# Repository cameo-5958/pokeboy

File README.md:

# Pokeboy

Game Boy handheld with its own emulator and a Gen 1 Pokemon battle AI that runs
on the device. No ROMs in here, bring your own.

## How the AI works

Trainers are driven by a small transformer with a GRU on top. It is integer
only: int8 weights, int16 hidden state, no floats on the device.

The patched ROM runs an unused opcode (`$DB`, `$EB`, `$EC`) wherever the game
would normally pick a trainer's move. The emulator traps it, reads the battle
out of WRAM, runs the model and writes the choice back.

One decision is too slow for a single frame on the Cortex-A8, so the model is
cut into small steps (one GEMM block, one attention head, one GRU step) and the
scheduler fits them in between frames. `ai/models/pep_int.py` is the reference
and the C++ in `pkai/` has to match it bit for bit. There is a test for that.

## Layout

- `gameboy/` emulator core, tests, tools
- `emulator/` frontends: linux, headless, win32
- `pkai/` battle AI
- `pred-patch/` pokered with the opcodes the AI hooks into
- `ai/` simulator, training, weight export
- `buildroot/` device image (PocketBeagle / OSD3358)
- `hardware/` KiCad project
- `app/` Expo app
- `backend/` API for ROMs, mods and cartridge metadata

## Build

```sh
# core, C++17
cmake -S gameboy -B build -DCMAKE_BUILD_TYPE=Release -DPKAI_BUILD_ROM=OFF
cmake --build build -j
build/gbemu_headless game.gb 1800 out.bmp

# patched ROM (needs rgbds) and AI
pred-patch/build_ai.sh
cd ai && uv sync --group dev && sim/build_engine.sh && scripts/build_pkai.sh

# device image
buildroot/scripts/build-image.sh
buildroot/scripts/qemu/run-system.sh

# backend (:4000) and app
cd backend && npm install && npm run dev
cd app && npm install && npm start
```

Most of the `pkai` tests skip themselves until the patched ROM and the weights
have been built.

## License

MIT, see `LICENSE`. `pred-patch/` is the pret/pokered disassembly under its own
terms, see `pred-patch/THIRD_PARTY_NOTICES.md`.

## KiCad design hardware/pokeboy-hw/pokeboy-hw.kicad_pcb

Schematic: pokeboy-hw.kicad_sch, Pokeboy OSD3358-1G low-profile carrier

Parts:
C1: 10n; C_0402_1005Metric
C2, C3, C4, C6, C10: 10u/10V; C_0402_1005Metric
C5, C9, C12, C15, C21, C25, C26, C27: 100n; C_0402_1005Metric
C7, C8: 22u/10V; C_0402_1005Metric
C11: 22u/6.3V; C_0402_1005Metric
C13: 1u/50V; C_0402_1005Metric
C14: 4.7u/10V; C_0402_1005Metric
C16: 220n; C_0402_1005Metric
C20: 10u; C_0402_1005Metric
C22, C23: 220p; C_0402_1005Metric
C24: 1u; C_0402_1005Metric
C102, C103: 18pF; C_0402_1005Metric
C105: 100nF; C_0402_1005Metric
C106: 10uF; C_0805_2012Metric
C107, C108, C109: 22u/10V; C_0805_2012Metric
D1: RED CHARGE; LED_0402_1005Metric
D2: GREEN POWER; LED_0402_1005Metric
D3: 60V Schottky; D_SOD-123F; MPN PMEG6010CEH
FB1, FB2: 600R@100MHz; L_0402_1005Metric
J1: USB Micro-B data/power; USB_Micro-B_Molex-105017-0001; MPN Molex 105017-0001
J2: LiPo 1S + / NTC / -; BATTERY_PADS_3
J3: POWER SWITCH PADS; SWITCH_PADS_2
J4: 8 OHM SPEAKER PADS; SPEAKER_PADS_2
J5: EA WF030-39S; EA_WF030_39S; MPN EA TFT020-23AINN + EA WF030-39S
J6: UART TEST PADS; TEST_PADS_3
J7: RECOVERY SHORT PADS; SHORT_PADS_2
J8: RESET SHORT PADS; SHORT_PADS_2
J9: 104031-0811; microSD_HC_Molex_104031-0811
L1: 0.47uH XFL4015; XFL4015; MPN XFL4015-471ME
L2: 2.2uH >1.5A; L_APV_ANR3012; MPN XFL3012-222MEB
L3: 10uH 1A; LQH43PN; MPN LQH43PN100MR0L
R3: 0R; R_0402_1005Metric
R4: 10k; R_0402_1005Metric; not fitted
R5: 1.78k 1%; R_0402_1005Metric
R6: 3.09k 1%; R_0402_1005Metric
R7: 3.01k 1%; R_0402_1005Metric
R8: 46.4k 1%; R_0402_1005Metric
R9: 10k DNP; R_0402_1005Metric; not fitted
R10, R11: 2.2k; R_0402_1005Metric
R12, R13, R18, R20, R21, R23, R26: 100k; R_0402_1005Metric
R14: 806k 1%; R_0402_1005Metric
R15: 91k 1%; R_0402_1005Metric
R16: 187k 1%; R_0402_1005Metric
R17: 100k 1%; R_0402_1005Metric
R19: 0R DNP; R_0402_1005Metric; not fitted
R22: 10R 1%; R_0402_1005Metric
R27, R28, R29, R30: 33R; R_0402_1005Metric
R31, R32, R104, R105, R106, R107, R108, R109: 10k; R_0402_1005Metric
R33: 1M 1%; R_0402_1005Metric
R34: 330k 1%; R_0402_1005Metric
R102: 1M; R_0402_1005Metric
RN1, RN2, RN3, RN4, RN5, RN6: 4x22R; R_Array_Convex_4x0603
RN7, RN8, RN9, RN10: 100k; R_Array_Convex_4x0603
SW1, SW2, SW3, SW4: EVQ-P1905M
SW5, SW6: B3AL-1001P
SW7, SW8: EVQ-P2B02B
U1: OSD3358-1G-ISM; OSD335X-BGA-256
U2: BQ24074RGT; VQFN-16-1EP_3x3mm_P0.5mm_EP1.6x1.6mm; MPN BQ24074RGT
U3: TPS63802DLAR; TPS63802_DLA10; MPN TPS63802DLAR
U4: TPS62162DSG; WSON-8-1EP_2x2mm_P0.5mm_EP0.9x1.6mm_ThermalVias; MPN TPS62162DSGR
U5: TPS61165DRV; WSON-6-1EP_2x2mm_P0.65mm_EP1x1.6mm; MPN TPS61165DRVR
U6: MAX98357AETE+T; TQFN-16-1EP_3x3mm_P0.5mm_EP1.23x1.23mm
U7: TPD2EUSB30; Texas_DRT-3; MPN TPD2EUSB30DRTR
Y1: 24 MHz; CRYSTAL_5X3.2MM

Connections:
/ADC_VREFN: U1.A9 (AGND_ADC), U1.B9 (VREFN)
/ADC_VREFP: U1.A7 (SYS_ADC_1P8V), U1.B7 (VREFP)
/AMP_EN: R26.1, U1.B4 (XDMA_EVENT_INTR1), U6.4 (SD_MODE)
/AMP_OUT_N: FB2.1, U6.10 (OUTN)
/AMP_OUT_P: FB1.1, U6.9 (OUTP)
/BAT_NTC: J2.2, R9.1, U2.1 (TS)
/BAT_PLUS: C3.1, J2.1, R33.1, U2.2 (BAT), U2.3 (BAT)
/BAT_SENSE: C27.1, R33.2, R34.1, U1.A8 (AIN0)
/BB_EN: R16.2, R17.1, U3.1
/BB_FB: R14.2, R15.1, U3.4
/BB_L1: L1.1, U3.9
/BB_L2: L1.2, U3.7
/BB_MODE: R19.2, R20.1, U3.2
/BB_PG: R18.2, U3.5
/BL_COMP: C16.1, U5.2 (COMP)
/BL_CTRL: R23.1, U1.C3 (MCASP0_AXR1), U5.5 (CTRL)
/BL_SW: D3.1 (K), L3.2, U5.4 (SW)
/BQ_ILIM: R6.1, U2.12 (ILIM)
/BQ_ISET: R5.1, U2.16 (ISET)
/BQ_ITERM: R7.1, U2.15 (ITERM)
/BQ_TMR: R8.1, U2.14 (TMR)
/BTN_A: SW6.1, U1.A13 (SPI0_SCLK)
/BTN_B: SW5.1, U1.A14 (SPI0_CS0)
/BTN_DOWN: SW3.1, U1.A11 (UART1_RXD)
/BTN_LEFT: SW1.1, U1.A3 (MCASP0_ACLKR)
/BTN_RIGHT: SW4.1, U1.A4 (XDMA_EVENT_INTR0)
/BTN_SELECT: SW7.1, U1.B1 (MCASP0_AHCLKR)
/BTN_START: SW8.1, U1.B3 (MCASP0_FSR)
/BTN_UP: SW2.1, U1.A10 (UART1_RTSN)
/BUCK_PG: R21.2, U4.8 (PG)
/BUCK_SW: L2.1, U4.7 (SW)
/CHG_ACTIVE_N: D1.2 (A), R12.2, U1.C13 (UART0_RTSN), U2.9 (~CHG)
/CHG_PGOOD_N: D2.2 (A), R13.2, U1.R7 (GPMC_CSN3), U2.7 (~PGOOD)
/I2S_BCLK: U1.A1 (MCASP0_ACLKX), U6.16 (BCLK)
/I2S_DOUT: U1.B2 (MCASP0_AXR0), U6.1 (DIN)
/I2S_LRCLK: U1.A2 (MCASP0_FSX), U6.14 (LRCLK)
/LCD_CLK_CORE: RN5.3 (R3.1), U1.F1 (LCD_PCLK)
/LCD_CLK_FPC: J5.23, RN5.6 (R3.2)
/LCD_D0_CORE: RN1.1 (R1.1), RN10.8 (R1.2), U1.G3 (LCD_DATA0)
/LCD_D0_FPC: J5.5, RN1.8 (R1.2)
/LCD_D1_CORE: RN1.2 (R2.1), RN10.7 (R2.2), U1.G2 (LCD_DATA1)
/LCD_D1_FPC: J5.6, RN1.7 (R2.2)
/LCD_D2_CORE: RN1.3 (R3.1), RN10.6 (R3.2), U1.G1 (LCD_DATA2)
/LCD_D2_FPC: J5.7, RN1.6 (R3.2)
/LCD_D3_CORE: RN1.4 (R4.1), RN10.5 (R4.2), U1.H3 (LCD_DATA3)
/LCD_D3_FPC: J5.8, RN1.5 (R4.2)
/LCD_D4_CORE: RN2.1 (R1.1), RN9.4 (R4.1), U1.H2 (LCD_DATA4)
/LCD_D4_FPC: J5.9, RN2.8 (R1.2)
/LCD_D5_CORE: RN2.2 (R2.1), RN9.3 (R3.1), U1.H1 (LCD_DATA5)
/LCD_D5_FPC: J5.10, RN2.7 (R2.2)
/LCD_D6_CORE: RN2.3 (R3.1), RN9.2 (R2.1), U1.J3 (LCD_DATA6)
/LCD_D6_FPC: J5.11, RN2.6 (R3.2)
/LCD_D7_CORE: RN2.4 (R4.1), RN9.1 (R1.1), U1.J2 (LCD_DATA7)
/LCD_D7_FPC: J5.12, RN2.5 (R4.2)
/LCD_D8_CORE: RN3.1 (R1.1), RN8.4 (R4.1), U1.J1 (LCD_DATA8)
/LCD_D8_FPC: J5.13, RN3.8 (R1.2)
/LCD_D9_CORE: RN3.2 (R2.1), RN8.3 (R3.1), U1.K3 (LCD_DATA9)
/LCD_D9_FPC: J5.14, RN3.7 (R2.2)
/LCD_D10_CORE: RN3.3 (R3.1), RN8.2 (R2.1), U1.K2 (LCD_DATA10)
/LCD_D10_FPC: J5.15, RN3.6 (R3.2)
/LCD_D11_CORE: RN3.4 (R4.1), RN8.1 (R1.1), U1.K1 (LCD_DATA11)
/LCD_D11_FPC: J5.16, RN3.5 (R4.2)
/LCD_D12_CORE: RN4.1 (R1.1), RN7.4 (R4.1), U1.L3 (LCD_DATA12)
/LCD_D12_FPC: J5.17, RN4.8 (R1.2)
/LCD_D13_CORE: RN4.2 (R2.1), RN7.3 (R3.1), U1.L2 (LCD_DATA13)
/LCD_D13_FPC: J5.18, RN4.7 (R2.2)
/LCD_D14_CORE: RN4.3 (R3.1), RN7.2 (R2.1), U1.L1 (LCD_DATA14)
/LCD_D14_FPC: J5.19, RN4.6 (R3.2)
/LCD_D15_CORE: RN4.4 (R4.1), RN7.1 (R1.1), U1.M3 (LCD_DATA15)
/LCD_D15_FPC: J5.20, RN4.5 (R4.2)
/LCD_D16_CORE: RN5.1 (R1.1), U1.P7 (GPMC_AD15)
/LCD_D16_FPC: J5.21, RN5.8 (R1.2)
/LCD_D17_CORE: RN5.2 (R2.1), U1.T6 (GPMC_AD14)
/LCD_D17_FPC: J5.22, RN5.7 (R2.2)
/LCD_DE_CORE: RN5.4 (R4.1), U1.E1 (LCD_AC_BIAS_EN)
/LCD_DE_FPC: J5.24, RN5.5 (R4.2)
/LCD_HSYNC_CORE: RN6.1 (R1.1), U1.F2 (LCD_HSYNC)
/LCD_HSYNC_FPC: J5.25, RN6.8 (R1.2)
/LCD_VSYNC_CORE: RN6.2 (R2.1), U1.F3 (LCD_VSYNC)
/LCD_VSYNC_FPC: J5.26, RN6.7 (R2.2)
/LED_A: C13.1, D3.2 (A), J5.2
/LED_CHG_A: D1.1 (K), R10.2
/LED_K: J5.1, R22.1, U5.1 (FB)
/LED_PG_A: D2.1 (K), R11.2
/NPOR: J8.1, R32.2, U1.R11 (WARMRSTN)
/OSD_1V8: U1.F10 (SYS_VDD_1P8V), U1.G10 (SYS_VDD_1P8V), U1.H10 (SYS_VDD_1P8V), U1.H11 (SYS_VDD_1P8V), U1.J10 (SYS_VDD_1P8V), U1.J11 (SYS_VDD_1P8V), U1.K10 (SYS_VDD_1P8V), U1.L10 (SYS_VDD_1P8V)
/OSD_3V3A: J9.4, R12.1, R13.1, R18.1, R32.1, R104.2, R105.2, R106.2, R107.2, R108.2, R109.2, U1.F8 (SYS_VDD3_3P3V), U1.F9 (VDDSHV4), U1.G8 (SYS_VDD3_3P3V), U1.G9 (VDDSHV5), U1.H7 (SYS_VDD3_3P3V), U1.H8 (SYS_VDD3_3P3V), U1.H9 (VDDSHV6), U1.J7 (SYS_VDD3_3P3V), U1.J8 (SYS_VDD3_3P3V), U1.J9 (VDDSHV1), U1.K8 (SYS_VDD3_3P3V), U1.K9 (VDDSHV2), U1.L8 (SYS_VDD3_3P3V), U1.L9 (VDDSHV3)
/OSD_3V3AUX: U1.F11 (SYS_VDD2_3P3V), U1.G11 (SYS_VDD2_3P3V)
/OSD_3V3B: C105.1, RN7.7 (R2.2), RN9.5 (R4.2), RN10.4 (R4.1), U1.F6 (SYS_VDD1_3P3V), U1.F7 (SYS_VDD1_3P3V), U1.G6 (SYS_VDD1_3P3V), U1.G7 (SYS_VDD1_3P3V)
/OSD_OSC_IN: C102.1, R102.1, U1.P16 (OSC0_IN), Y1.2
/OSD_OSC_OUT: C103.1, R102.2, U1.N16 (OSC0_OUT), Y1.1
/OSD_RTC_1V8: U1.K11 (SYS_RTC_1P8V), U1.L11 (SYS_RTC_1P8V)
/OSD_SYS: C107.1, C108.1, C109.1, U1.K6 (SYS_VOUT), U1.K7 (SYS_VOUT), U1.L6 (SYS_VOUT), U1.L7 (SYS_VOUT)
/PMIC_PGOOD: U1.N12 (PMIC_PGOOD), U1.P11 (PWRONRSTN)
/PMIC_PWR_EN: U1.N10 (PMIC_POWER_EN), U1.N11 (PMIC_PWR_EN)
/PWR_SW: J3.2, R16.1
/RECOVERY: J7.1, U1.C1 (TDI)
/RTC_PWRONRSTN: U1.N4 (PMIC_LDO_PGOOD), U1.N5 (RTC_PWRONRSTN)
/SD_CD_N: J9.9, R109.1, U1.C14 (SPI0_CS1)
/SD_CLK: J9.5, U1.B15 (MMC0_CLK)
/SD_CMD: J9.3, R108.1, U1.B16 (MMC0_CMD)
/SD_D0: J9.7, R104.1, U1.A16 (MMC0_DAT0)
/SD_D1: J9.8, R105.1, U1.A15 (MMC0_DAT1)
/SD_D2: J9.1, R106.1, U1.C16 (MMC0_DAT2)
/SD_D3: J9.2, R107.1, U1.C15 (MMC0_DAT3)
/SPK_N: C23.1, FB2.2, J4.2
/SPK_P: C22.1, FB1.2, J4.1
/SYS_5V: C7.1, C8.1, C9.1, C10.1, C14.1, C15.1, C20.1, C21.1, C106.1, L3.1, R14.1, U1.P10 (VIN_AC), U1.R10 (VIN_AC), U1.T10 (VIN_AC), U3.6, U4.2 (VIN), U4.3 (EN), U5.6 (VIN), U6.7 (VDD), U6.8 (VDD)
/SYS_BAT: C4.1, C6.1, J3.1, R10.1, R11.1, U2.10 (OUT), U2.11 (OUT), U3.10
/TFT_DC: J5.32, R29.2
/TFT_DC_CORE: R29.1, U1.C5 (ECAP0_IN_PWM0_OUT)
/TFT_RESET: J5.33, R30.2, R31.2
/TFT_RESET_CORE: R30.1, U1.C12 (UART0_CTSN)
/TFT_SCL: J5.31, R27.2
/TFT_SCL_CORE: R27.1, U1.C10 (I2C0_SCL)
/TFT_SDA: J5.29, R28.2
/TFT_SDA_CORE: R28.1, U1.C11 (I2C0_SDA)
/UART0_RX: J6.2, U1.A12 (UART0_RXD)
/UART0_TX: J6.1, U1.B12 (UART0_TXD)
/USB_VBUSDET: C1.1, R3.2, R4.1, U1.J16 (USB0_VBUS)
/VIN_BAT: U1.N7 (PMIC_BAT_SENSE), U1.P8 (VIN_BAT), U1.R8 (VIN_BAT), U1.T8 (VIN_BAT)

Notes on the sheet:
DESIGN INTENT: panel covers the 30x30 mm Core1106; the carrier aperture clears underside parts. The modelled top envelope is about 2.6 mm, leaving ~0.6 mm nominal in a 3.2 mm cavity. Specify inside-corner radius <=0.75 mm and validate solder standoff, display fit, and thermals on first article.
DISPLAY FIRMWARE: RGB666 data D0-D17 plus CLK/DE/HSYNC/VSYNC. ST7789V serial setup uses SDA/SCL/D-C/RESET; RGB-mode CS and TE are intentionally not connected. Initial timing target: ~17 MHz pixel clock, HS 30/HBP 30/HFP 60, VS 4/VBP 4/VFP 8; validate against the exact panel lot.

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
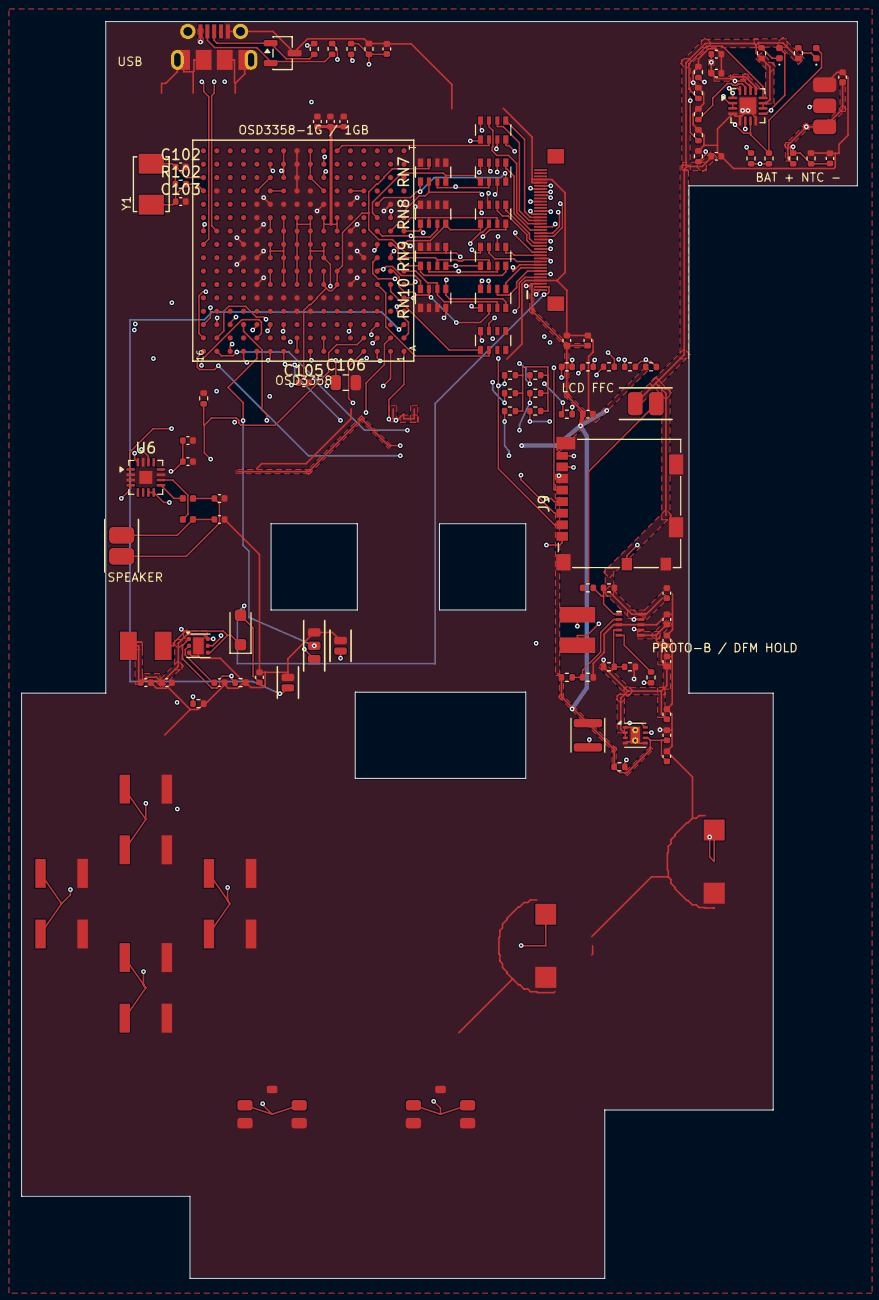
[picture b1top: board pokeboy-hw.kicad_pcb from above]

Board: 4 copper layers, 79.4 x 119.4 mm, 113 parts (0 on the bottom side), 128 nets.

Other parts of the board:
R1, R2: 0R; R_0402_1005Metric

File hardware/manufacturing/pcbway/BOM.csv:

Item,Qty,Designators,Value,Footprint,Manufacturer,Manufacturer Part Number,Assembly,Substitution note
1,1,U1,AM3358 + 1GB DDR3L,21x21mm 256-BGA 1.27mm,Octavo Systems,OSD3358-1G-ISM,SMT BGA,No substitution; consign; X-ray
2,1,U2,1S Li-ion charger/power path,VQFN-16,Texas Instruments,BQ24074RGT,SMT,No substitution
3,1,U3,5V buck-boost,TPS63802 DLA10,Texas Instruments,TPS63802DLAR,SMT,No substitution
4,1,U4,3.3V buck,WSON-8,Texas Instruments,TPS62162DSGR,SMT,No substitution
5,1,U5,LED boost,WSON-6,Texas Instruments,TPS61165DRVR,SMT,No substitution
6,1,U6,I2S mono class-D,TQFN-16,Analog Devices,MAX98357AETE+T,SMT,No substitution
7,1,U7,USB ESD,SOT-23,Texas Instruments,TPD2EUSB30DRTR,SMT,No substitution
8,1,J1,Micro-USB B,105017 footprint,Molex,1050170001,SMT,No substitution
9,1,J9,microSD push-push,104031 footprint,Molex,1040310811,SMT,No substitution
10,4,SW1 SW2 SW3 SW4,D-pad tactile,Pokeboy EVQ-P1905M,Panasonic,EVQ-P1905M,SMT,No substitution
11,2,SW5 SW6,A/B tactile,Pokeboy B3AL-1001P,Omron,B3AL-1001P,SMT,No substitution
12,2,SW7 SW8,Start/Select tactile,Pokeboy EVQ-P2B02B,Panasonic,EVQ-P2B02B,SMT,No substitution
13,1,Y1,24MHz crystal,5.0x3.2mm 2-pad,CTS,445A35A24M00000,SMT,Verify lifecycle or consign exact
14,1,L1,0.47uH,XFL4015,Coilcraft,XFL4015-471MEC,SMT,No substitution without power review
15,1,L2,2.2uH,NRS3012,Taiyo Yuden,NRS3012T2R2MMGJ,SMT,Equivalent >=1.5A permitted
16,1,L3,10uH,LQH43PN,Murata,LQH43PN100M26L,SMT,Equivalent >=1A permitted; 2.80 mm MAX height (Murata JELF243A-0093); low-profile alt Coilcraft XGL4040-103 (2.10 mm max) needs 4.0x4.0 land
17,2,FB1 FB2,600ohm at 100MHz,0402,Murata,BLM15AG601SN1D,SMT,Equivalent permitted
18,1,D1,Red LED,0402,Lite-On,LTST-C191KRKT,SMT,Equivalent color/current permitted
19,1,D2,Green LED,0402,Lite-On,LTST-C191KGKT,SMT,Equivalent color/current permitted
20,1,D3,60V Schottky,SOD-123F,Nexperia,PMEG6010CEH115,SMT,Equal or better permitted
21,1,C1,10nF 16V X7R,0402,Murata,GRM155R71C103KA88D,SMT,Equivalent permitted
22,5,C2 C3 C4 C6 C10,10uF 10V X5R,0402,Murata,GRM155R61A106ME11D,SMT,No lower voltage
23,5,C7 C8 C107 C108 C109,22uF 10V X5R,0402,Murata,GRM155R61A226ME11D,SMT,Verify effective capacitance; C107-C109 are the SYS_VOUT bulk bank (Octavo PD4)
24,1,C11,22uF 6.3V X5R,0402,Murata,GRM155R60J226ME11D,SMT,Verify effective capacitance
25,9,C5 C9 C12 C15 C21 C25 C26 C27 C105,100nF 16V X7R,0402,Murata,GRM155R71C104KA88D,SMT,Equivalent permitted
26,1,C13,1uF 50V X5R,0402,Murata,GRM155R61H105KE11D,SMT,No lower voltage
27,1,C14,4.7uF 10V X5R,0402,Murata,GRM155R61A475MEAAD,SMT,Equivalent permitted
28,1,C16,220nF 10V X7R,0402,Murata,GRM155R71A224KA01D,SMT,Equivalent permitted
29,1,C20,10uF 6.3V X5R,0402,Murata,GRM155R60J106ME15D,SMT,Equivalent permitted
30,2,C22 C23,220pF 50V C0G,0402,Murata,GRM1555C1H221JA01D,SMT,Equivalent C0G permitted
31,1,C24,1uF 10V X5R,0402,Murata,GRM155R61A105KE15D,SMT,Equivalent permitted
32,2,C102 C103,18pF 50V C0G,0402,Murata,GRM1555C1H180JA01D,SMT,Match crystal load calculation
33,1,C106,10uF 10V X5R,0805,Murata,GRM21BR61A106KE19L,SMT,Equivalent permitted
34,3,R1 R2 R3,0ohm,0402,Yageo,RC0402JR-070RL,SMT,R1/R2 were 22ohm series on USB DP/DM (prohibited by Octavo UB2); R3 was 10k VBUS divider top (UB1) - all now 0ohm links
35,2,R10 R11,2.2kohm 1%,0402,Yageo,RC0402FR-072K2L,SMT,Equivalent permitted
36,8,R31 R32 R104 R105 R106 R107 R108 R109,10kohm 1%,0402,Yageo,RC0402FR-0710KL,SMT,Equivalent permitted
37,8,R12 R13 R17 R18 R20 R21 R23 R26,100kohm 1%,0402,Yageo,RC0402FR-07100KL,SMT,Equivalent permitted
38,1,R14,806kohm 1%,0402,Yageo,RC0402FR-07806KL,SMT,Equivalent permitted
39,1,R15,91kohm 1%,0402,Yageo,RC0402FR-0791KL,SMT,Equivalent permitted
40,1,R16,187kohm 1%,0402,Yageo,RC0402FR-07187KL,SMT,Equivalent permitted
41,1,R22,10ohm 1%,0402,Yageo,RC0402FR-0710RL,SMT,Equivalent permitted
42,4,R27 R28 R29 R30,33ohm 1%,0402,Yageo,RC0402FR-0733RL,SMT,Equivalent permitted
43,2,R33 R102,1Mohm 1%,0402,Yageo,RC0402FR-071ML,SMT,Equivalent permitted
44,1,R34,330kohm 1%,0402,Yageo,RC0402FR-07330KL,SMT,Equivalent permitted
45,1,R5,1.78kohm 1%,0402,Yageo,RC0402FR-071K78L,SMT,Equivalent permitted
46,1,R6,3.09kohm 1%,0402,Yageo,RC0402FR-073K09L,SMT,Equivalent permitted
47,1,R7,3.01kohm 1%,0402,Yageo,RC0402FR-073K01L,SMT,Equivalent permitted
48,1,R8,46.4kohm 1%,0402,Yageo,RC0402FR-0746K4L,SMT,Equivalent permitted
49,1,R19,0ohm,0402,Yageo,RC0402JR-070RL,DNP,Do not fit
50,1,R9,10kohm,0402,Yageo,RC0402FR-0710KL,DNP,Do not fit
57,1,R4,10kohm,0402,Yageo,RC0402FR-0710KL,DNP,Do not fit; was VBUS divider bottom - deleted so USB0_VBUS sees 5 V (Octavo UB1)
51,6,RN1 RN2 RN3 RN4 RN5 RN6,4x22ohm,4x0603 convex,Yageo,YC164-JR-0722RL,SMT,No substitution without SI review
52,4,RN7 RN8 RN9 RN10,4x100kohm,4x0603 convex,Yageo,YC164-JR-07100KL,SMT,Keep exact SYSBOOT pattern
53,1,J5,EA TFT020-23AINN RGB666,39-pin display footprint,DISPLAY VISIONS,EA TFT020-23AINN,OFF-BOARD,Final assembly only
54,1,J2,Protected 1S LiPo with 10k NTC,Wire pads,User supplied,USER-SUPPLIED-LIPO-1S-NTC,OFF-BOARD,Polarity and NTC mandatory
55,1,J4,8ohm speaker,Wire pads,User supplied,USER-SUPPLIED-8OHM-SPEAKER,OFF-BOARD,Final assembly only
56,1,MICROSD,Validated boot card,microSD,User supplied,USER-SUPPLIED-MICROSD,OFF-BOARD,Program before functional test
